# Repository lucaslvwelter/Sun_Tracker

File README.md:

Trabalho de TIM de Sistemas Microprocessados 2.

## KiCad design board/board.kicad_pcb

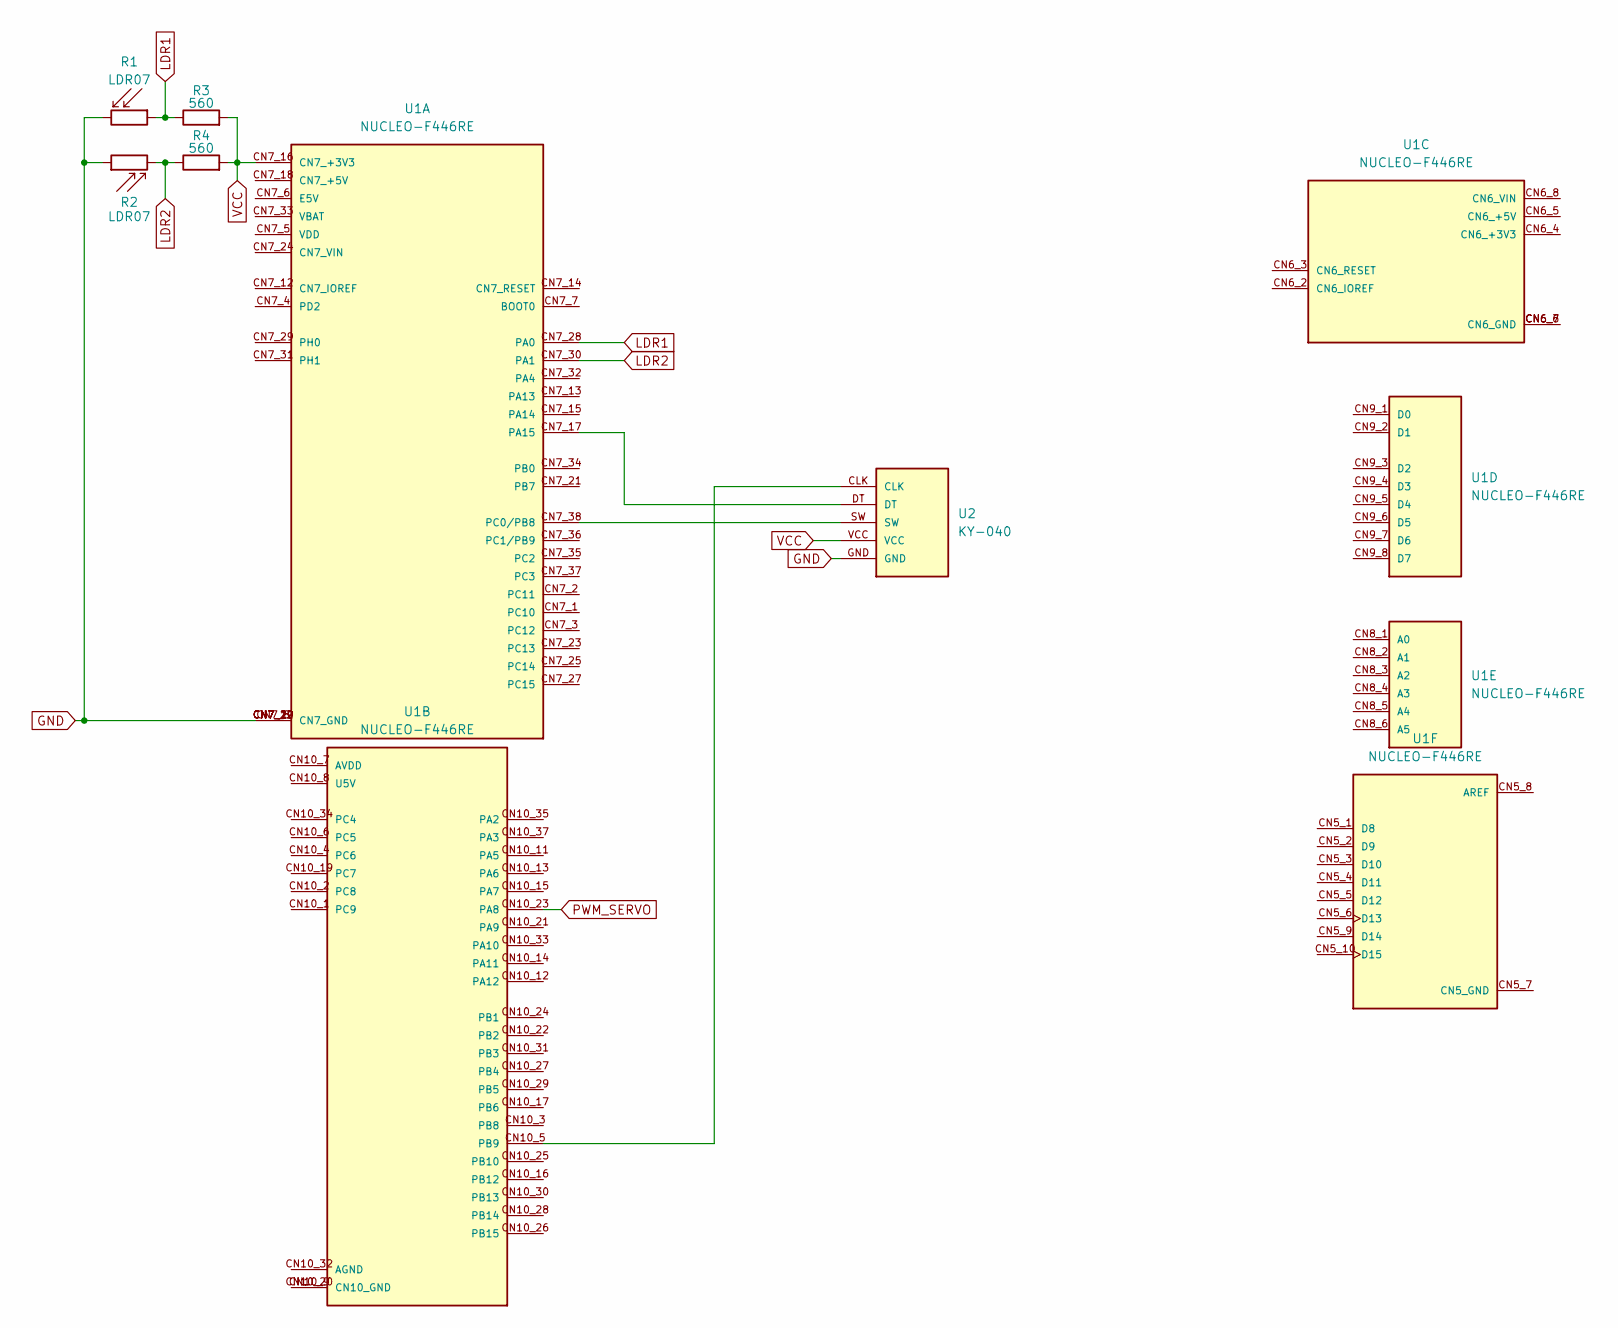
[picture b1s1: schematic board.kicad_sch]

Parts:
R1, R2: LDR07; R_LDR_5.1x4.3mm_P3.4mm_Vertical
R3, R4: 560; R_Axial_DIN0204_L3.6mm_D1.6mm_P5.08mm_Horizontal
U1: NUCLEO-F446RE; MODULE_NUCLEO-F446RE; PARTREV 13
U2: KY-040; KY-040-PORT

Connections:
GND: R1.2, R2.1, U1.CN7_8 (CN7_GND), U1.CN7_19 (CN7_GND), U1.CN7_20 (CN7_GND), U1.CN7_22 (CN7_GND), U2.GND
LDR1: R1.1, R3.1, U1.CN7_28 (PA0)
LDR2: R2.2, R4.1, U1.CN7_30 (PA1)
unnamed: U1.CN7_17 (PA15), U2.DT
unnamed: U1.CN7_38 (PC0/PB8), U2.SW
unnamed: U1.CN10_9 (CN10_GND), U1.CN10_20 (CN10_GND)
unnamed: U1.CN10_5 (PB9), U2.CLK
unnamed: U1.CN6_6 (CN6_GND), U1.CN6_7 (CN6_GND)
PWM_SERVO: U1.CN10_23 (PA8)
VCC: R3.2, R4.2, U1.CN7_16 (CN7_+3V3), U2.VCC

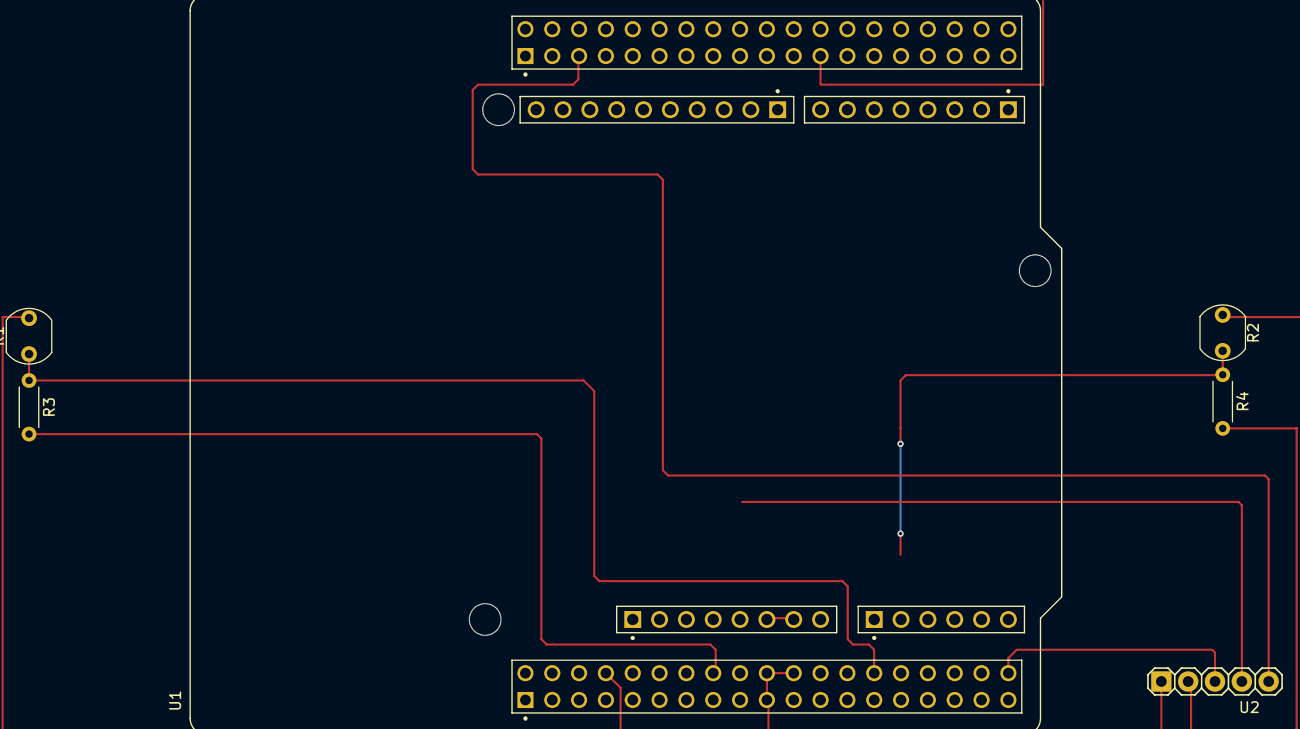
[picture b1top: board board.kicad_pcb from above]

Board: 2 copper layers, 6 parts (0 on the bottom side), 9 nets.

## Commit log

2025-07-15 Criei um arquivo de teste para o servo.
2025-07-18 Criei um arquivo para testar o ADC. Potenciômetro conectado ao PA0 para controlar o brilho de um LED.
2025-07-23 Corrigi a frequência do sinal gerado pelo teste do ADC. Possível solução para o problema do motor.
2025-07-26 Ajustei a escala do ADC para funcionar melhor com o potenciômetro.
2025-07-30 Comecei o projeto. Tentei controlar a posição de acordo com o valor dos LDRs, mas não funcionou.
2025-08-01 Implementei uma possível solução para a movimentação do motor, falta testar.
2025-08-12 Corrigi a movimentação do motor. Talvez precise mudar a normalização para ficar menos sensível, mas ainda preciso testar com a luz apagada (lâmpada tá influenciando).
2025-08-12 Implementei um output compare para enviar um relatório a cada 10 segundos. Falta testar.
2025-08-14 Adicionei o envio de um formulário para o monitor, mas o monitor não tá exibindo.
2025-08-14 Adicionei o controle manual do servo via encoder. Próximo passo é retomar o controle automático e adicionar o controle manual de forma opcional.
2025-08-15 Combinei o controle automático junto do controle manual. Também corrigi o relatório via terminal. Falta testar.
2025-08-18 Adicionei os detalhes que faltavam no projeto (botão do encoder que estava com ruído, e salvar a posição na troca de modos.
2025-09-02 Corri o JSON do Monitor e ajustei o código para fazer o envio da angulação corretamente.
2025-09-04 Implementei o uso de DMA na conversão dos ADCs.
2026-06-22 Remove metadata files
